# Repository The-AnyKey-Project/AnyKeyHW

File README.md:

# AnyKeyHW
Hardware for configurable macro keyboard with displays

## Inspired by
https://github.com/CoretechR/Keybon

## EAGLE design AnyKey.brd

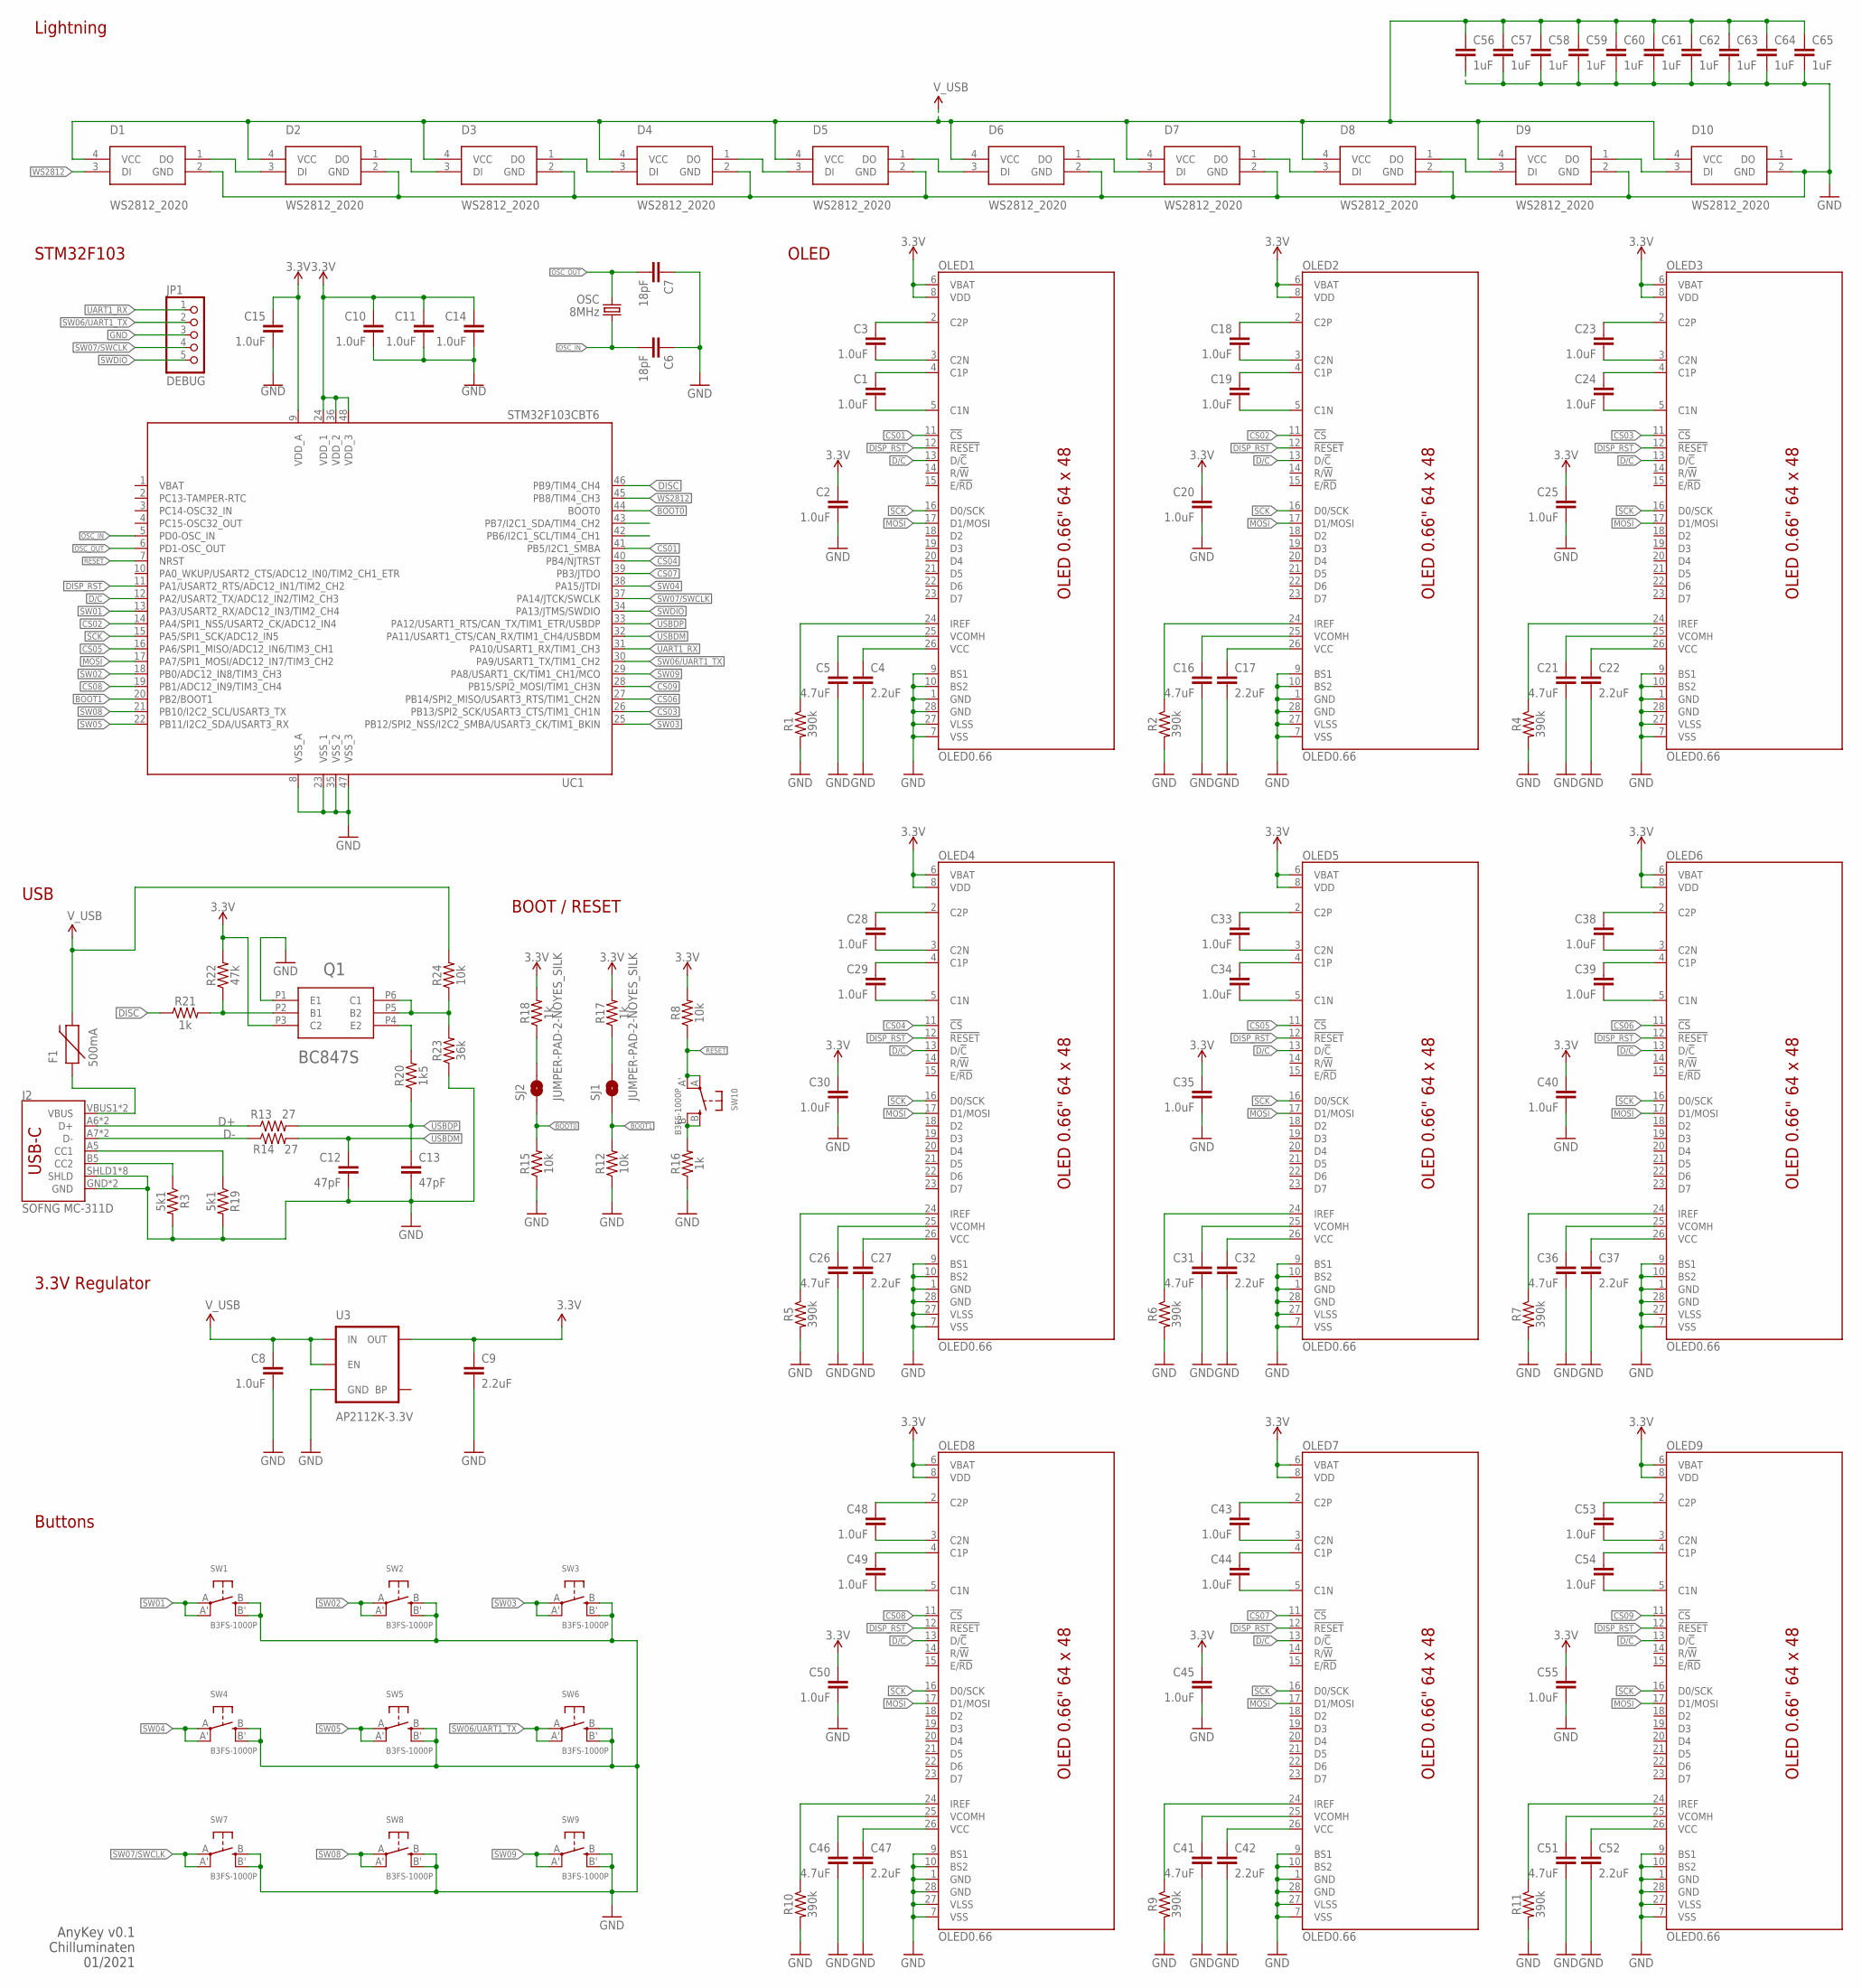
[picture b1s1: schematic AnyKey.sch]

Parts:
C1, C2, C3, C8, C10, C11, C14, C15, C18, C19, C20, C23, C24, C25, C28, C29, C30, C33, C34, C35, C38, C39, C40, C43, C44, C45, C48, C49, C50, C53, C54, C55: 1.0uF; 0603
C4, C9, C17, C22, C27, C32, C37, C42, C47, C52: 2.2uF; 0603
C5, C16, C21, C26, C31, C36, C41, C46, C51: 4.7uF; 0603
C6, C7: 18pF; 0603
C12, C13: 47pF; 0603
C56, C57, C58, C59, C60, C61, C62, C63, C64, C65: 1uF; 0603
D1, D2, D3, D4, D5, D6, D7, D8, D9, D10: WS2812_2020
F1: 500mA; PTC-1206
J2: SOFNG MC-311D; USB-C-16P
JP1: DEBUG; 1X05/90
OLED1, OLED2, OLED3, OLED4, OLED5, OLED6, OLED7, OLED8, OLED9: OLED0.66; OLED-0.66-64X48
OSC: 8MHz; CRYSTAL-SMD-5X3
Q1: BC847S; SOT-363
R1, R2, R4, R5, R6, R7, R9, R10, R11: 390k; 0603
R3, R19: 5k1; 0603
R8, R12, R15, R24: 10k; 0603
R13, R14: 27; 0603
R16, R17, R18, R21: 1k; 0603
R20: 1k5; 0603
R22: 47k; 0603
R23: 36k; 0603
SJ1, SJ2: JUMPER-PAD-2-NOYES_SILK; PAD-JUMPER-2-NO_YES_SILK
SW1, SW2, SW3, SW4, SW5, SW6, SW7, SW8, SW9, SW10: B3FS-1000P; EVQ-Q2_SMALLER
U3: AP2112K-3.3V; SOT23-5
UC1: STM32F103CBT6; LQFP48

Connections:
3.3V: C2.1, C9.1, C10.1, C11.1, C14.1, C15.1, C20.1, C25.1, C30.1, C35.1, C40.1, C45.1, C50.1, C55.1, OLED1.6 (VBAT), OLED1.8 (VDD), OLED2.6 (VBAT), OLED2.8 (VDD), OLED3.6 (VBAT), OLED3.8 (VDD), OLED4.6 (VBAT), OLED4.8 (VDD), OLED5.6 (VBAT), OLED5.8 (VDD), OLED6.6 (VBAT), OLED6.8 (VDD), OLED7.6 (VBAT), OLED7.8 (VDD), OLED8.6 (VBAT), OLED8.8 (VDD), OLED9.6 (VBAT), OLED9.8 (VDD), Q1.P3 (C2), R8.2, R17.2, R18.2, R22.2, U3.5 (OUT), UC1.9 (VDD_A), UC1.24 (VDD_1), UC1.36 (VDD_2), UC1.48 (VDD_3)
BOOT0: R15.2, SJ2.1, UC1.44 (BOOT0)
BOOT1: R12.2, SJ1.1, UC1.20 (PB2/BOOT1)
C1N: C1.2, OLED1.5 (C1N)
C1N1: C19.2, OLED2.5 (C1N)
C1N2: C24.2, OLED3.5 (C1N)
C1N3: C29.2, OLED4.5 (C1N)
C1N4: C34.2, OLED5.5 (C1N)
C1N5: C39.2, OLED6.5 (C1N)
C1N6: C44.2, OLED7.5 (C1N)
C1N7: C49.2, OLED8.5 (C1N)
C1N8: C54.2, OLED9.5 (C1N)
C1P: C1.1, OLED1.4 (C1P)
C1P1: C19.1, OLED2.4 (C1P)
C1P2: C24.1, OLED3.4 (C1P)
C1P3: C29.1, OLED4.4 (C1P)
C1P4: C34.1, OLED5.4 (C1P)
C1P5: C39.1, OLED6.4 (C1P)
C1P6: C44.1, OLED7.4 (C1P)
C1P7: C49.1, OLED8.4 (C1P)
C1P8: C54.1, OLED9.4 (C1P)
C2N: C3.2, OLED1.3 (C2N)
C2N1: C18.2, OLED2.3 (C2N)
C2N2: C23.2, OLED3.3 (C2N)
C2N3: C28.2, OLED4.3 (C2N)
C2N4: C33.2, OLED5.3 (C2N)
C2N5: C38.2, OLED6.3 (C2N)
C2N6: C43.2, OLED7.3 (C2N)
C2N7: C48.2, OLED8.3 (C2N)
C2N8: C53.2, OLED9.3 (C2N)
C2P: C3.1, OLED1.2 (C2P)
C2P1: C18.1, OLED2.2 (C2P)
C2P2: C23.1, OLED3.2 (C2P)
C2P3: C28.1, OLED4.2 (C2P)
C2P4: C33.1, OLED5.2 (C2P)
C2P5: C38.1, OLED6.2 (C2P)
C2P6: C43.1, OLED7.2 (C2P)
C2P7: C48.1, OLED8.2 (C2P)
C2P8: C53.1, OLED9.2 (C2P)
CS01: OLED1.11 (!CS!), UC1.41 (PB5/I2C1_SMBA)
CS02: OLED2.11 (!CS!), UC1.14 (PA4/SPI1_NSS/USART2_CK/ADC12_IN4)
CS03: OLED3.11 (!CS!), UC1.26 (PB13/SPI2_SCK/USART3_CTS/TIM1_CH1N)
CS04: OLED4.11 (!CS!), UC1.40 (PB4/NJTRST)
CS05: OLED5.11 (!CS!), UC1.16 (PA6/SPI1_MISO/ADC12_IN6/TIM3_CH1)
CS06: OLED6.11 (!CS!), UC1.27 (PB14/SPI2_MISO/USART3_RTS/TIM1_CH2N)
CS07: OLED7.11 (!CS!), UC1.39 (PB3/JTDO)
CS08: OLED8.11 (!CS!), UC1.19 (PB1/ADC12_IN9/TIM3_CH4)
CS09: OLED9.11 (!CS!), UC1.28 (PB15/SPI2_MOSI/TIM1_CH3N)
D+: J2.A6 (D+), J2.B6 (D+), R13.1
D-: J2.A7 (D-), J2.B7 (D-), R14.1
D/C: OLED1.13 (D/!C!), OLED2.13 (D/!C!), OLED3.13 (D/!C!), OLED4.13 (D/!C!), OLED5.13 (D/!C!), OLED6.13 (D/!C!), OLED7.13 (D/!C!), OLED8.13 (D/!C!), OLED9.13 (D/!C!), UC1.12 (PA2/USART2_TX/ADC12_IN2/TIM2_CH3)
DISC: R21.1, UC1.46 (PB9/TIM4_CH4)
DISP_RST: OLED1.12 (!RESET!), OLED2.12 (!RESET!), OLED3.12 (!RESET!), OLED4.12 (!RESET!), OLED5.12 (!RESET!), OLED6.12 (!RESET!), OLED7.12 (!RESET!), OLED8.12 (!RESET!), OLED9.12 (!RESET!), UC1.11 (PA1/USART2_RTS/ADC12_IN1/TIM2_CH2)
GND: C2.2, C4.2, C5.2, C6.1, C7.1, C8.2, C9.2, C10.2, C11.2, C12.2, C13.2, C14.2, C15.2, C16.2, C17.2, C20.2, C21.2, C22.2, C25.2, C26.2, C27.2, C30.2, C31.2, C32.2, C35.2, C36.2, C37.2, C40.2, C41.2, C42.2, C45.2, C46.2, C47.2, C50.2, C51.2, C52.2, C55.2, C56.2, C57.2, C58.2, C59.2, C60.2, C61.2, C62.2, C63.2, C64.2, C65.2, D1.2 (GND), D2.2 (GND), D3.2 (GND), D4.2 (GND), D5.2 (GND), D6.2 (GND), D7.2 (GND), D8.2 (GND), D9.2 (GND), D10.2 (GND), J2.GND, J2.GND2 (GND), J2.SHLD1 (SHLD), J2.SHLD2 (SHLD), J2.SHLD3 (SHLD), J2.SHLD4 (SHLD), J2.SHLD5 (SHLD), J2.SHLD6 (SHLD), J2.SHLD7 (SHLD), J2.SHLD8 (SHLD), JP1.3, OLED1.1 (GND), OLED1.7 (VSS), OLED1.9 (BS1), OLED1.10 (BS2), OLED1.27 (VLSS), OLED1.28 (GND), OLED2.1 (GND), OLED2.7 (VSS), OLED2.9 (BS1), OLED2.10 (BS2), OLED2.27 (VLSS), OLED2.28 (GND), OLED3.1 (GND), OLED3.7 (VSS), OLED3.9 (BS1), OLED3.10 (BS2), OLED3.27 (VLSS), OLED3.28 (GND), OLED4.1 (GND), OLED4.7 (VSS), OLED4.9 (BS1), OLED4.10 (BS2), OLED4.27 (VLSS), OLED4.28 (GND), OLED5.1 (GND), OLED5.7 (VSS), OLED5.9 (BS1), OLED5.10 (BS2), OLED5.27 (VLSS), OLED5.28 (GND), OLED6.1 (GND), OLED6.7 (VSS), OLED6.9 (BS1), OLED6.10 (BS2), OLED6.27 (VLSS), OLED6.28 (GND), OLED7.1 (GND), OLED7.7 (VSS), OLED7.9 (BS1), OLED7.10 (BS2), OLED7.27 (VLSS), OLED7.28 (GND), OLED8.1 (GND), OLED8.7 (VSS), OLED8.9 (BS1), OLED8.10 (BS2), OLED8.27 (VLSS), OLED8.28 (GND), OLED9.1 (GND), OLED9.7 (VSS), OLED9.9 (BS1), OLED9.10 (BS2), OLED9.27 (VLSS), OLED9.28 (GND), Q1.P1 (E1), R1.2, R2.2, R3.2, R4.2, R5.2, R6.2, R7.2, R9.2, R10.2, R11.2, R12.1, R15.1, R16.1, R19.2, R23.1, SW1.B (S), SW1.B' (S1), SW2.B (S), SW2.B' (S1), SW3.B (S), SW3.B' (S1), SW4.B (S), SW4.B' (S1), SW5.B (S), SW5.B' (S1), SW6.B (S), SW6.B' (S1), SW7.B (S), SW7.B' (S1), SW8.B (S), SW8.B' (S1), SW9.B (S), SW9.B' (S1), U3.2 (GND), UC1.8 (VSS_A), UC1.23 (VSS_1), UC1.35 (VSS_2), UC1.47 (VSS_3)
IREF: OLED1.24 (IREF), R1.1
IREF1: OLED2.24 (IREF), R2.1
IREF2: OLED3.24 (IREF), R4.1
IREF3: OLED4.24 (IREF), R5.1
IREF4: OLED5.24 (IREF), R6.1
IREF5: OLED6.24 (IREF), R7.1
IREF6: OLED7.24 (IREF), R9.1
IREF7: OLED8.24 (IREF), R10.1
IREF8: OLED9.24 (IREF), R11.1
MOSI: OLED1.17 (D1/MOSI), OLED2.17 (D1/MOSI), OLED3.17 (D1/MOSI), OLED4.17 (D1/MOSI), OLED5.17 (D1/MOSI), OLED6.17 (D1/MOSI), OLED7.17 (D1/MOSI), OLED8.17 (D1/MOSI), OLED9.17 (D1/MOSI), UC1.17 (PA7/SPI1_MOSI/ADC12_IN7/TIM3_CH2)
unnamed: R16.2, SW10.B (S), SW10.B' (S1)
unnamed: R18.1, SJ2.2
unnamed: R17.1, SJ1.2
unnamed: C4.1, OLED1.26 (VCC)
unnamed: C17.1, OLED2.26 (VCC)
unnamed: C22.1, OLED3.26 (VCC)
unnamed: C37.1, OLED6.26 (VCC)
unnamed: C32.1, OLED5.26 (VCC)
unnamed: J2.A5 (CC1), R19.1
unnamed: C27.1, OLED4.26 (VCC)
unnamed: J2.B5 (CC2), R3.1
unnamed: C47.1, OLED8.26 (VCC)
unnamed: C42.1, OLED7.26 (VCC)
unnamed: C52.1, OLED9.26 (VCC)
unnamed: Q1.P4 (E2), R20.2
unnamed: Q1.P5 (B2), Q1.P6 (C1), R23.2, R24.1
unnamed: Q1.P2 (B1), R21.2, R22.1
unnamed: D1.1 (DO), D2.3 (DI)
unnamed: D2.1 (DO), D3.3 (DI)
unnamed: D3.1 (DO), D4.3 (DI)
unnamed: D4.1 (DO), D5.3 (DI)
unnamed: D5.1 (DO), D6.3 (DI)
unnamed: D6.1 (DO), D7.3 (DI)
unnamed: D7.1 (DO), D8.3 (DI)
unnamed: D8.1 (DO), D9.3 (DI)
unnamed: D9.1 (DO), D10.3 (DI)
OSC_IN: C6.2, OSC.1, UC1.5 (PD0-OSC_IN)
OSC_OUT: C7.2, OSC.3 (2), UC1.6 (PD1-OSC_OUT)
RESET: R8.1, SW10.A, SW10.A' (P1), UC1.7 (NRST)
SCK: OLED1.16 (D0/SCK), OLED2.16 (D0/SCK), OLED3.16 (D0/SCK), OLED4.16 (D0/SCK), OLED5.16 (D0/SCK), OLED6.16 (D0/SCK), OLED7.16 (D0/SCK), OLED8.16 (D0/SCK), OLED9.16 (D0/SCK), UC1.15 (PA5/SPI1_SCK/ADC12_IN5)
SW01: SW1.A, SW1.A' (P1), UC1.13 (PA3/USART2_RX/ADC12_IN3/TIM2_CH4)
SW02: SW2.A, SW2.A' (P1), UC1.18 (PB0/ADC12_IN8/TIM3_CH3)
SW03: SW3.A, SW3.A' (P1), UC1.25 (PB12/SPI2_NSS/I2C2_SMBA/USART3_CK/TIM1_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)
SW04: SW4.A, SW4.A' (P1), UC1.38 (PA15/JTDI)
SW05: SW5.A, SW5.A' (P1), UC1.22 (PB11/I2C2_SDA/USART3_RX)
SW06/UART1_TX: JP1.2, SW6.A, SW6.A' (P1), UC1.30 (PA9/USART1_TX/TIM1_CH2)
SW07/SWCLK: JP1.4, SW7.A, SW7.A' (P1), UC1.37 (PA14/JTCK/SWCLK)
SW08: SW8.A, SW8.A' (P1), UC1.21 (PB10/I2C2_SCL/USART3_TX)
SW09: SW9.A, SW9.A' (P1), UC1.29 (PA8/USART1_CK/TIM1_CH1/MCO)
SWDIO: JP1.5, UC1.34 (PA13/JTMS/SWDIO)
UART1_RX: JP1.1, UC1.31 (PA10/USART1_RX/TIM1_CH3)
USBDM: C12.1, R14.2, UC1.32 (PA11/USART1_CTS/CAN_RX/TIM1_CH4/USBDM)
USBDP: C13.1, R13.2, R20.1, UC1.33 (PA12/USART1_RTS/CAN_TX/TIM1_ETR/USBDP)
VBAT: UC1.1 (VBAT)
VCOMH: C5.1, OLED1.25 (VCOMH)
VCOMH1: C16.1, OLED2.25 (VCOMH)
VCOMH2: C21.1, OLED3.25 (VCOMH)
VCOMH3: C26.1, OLED4.25 (VCOMH)
VCOMH4: C31.1, OLED5.25 (VCOMH)
VCOMH5: C36.1, OLED6.25 (VCOMH)
VCOMH6: C41.1, OLED7.25 (VCOMH)
VCOMH7: C46.1, OLED8.25 (VCOMH)
VCOMH8: C51.1, OLED9.25 (VCOMH)
VUSB-RAW: F1.1, J2.VBUS1 (VBUS), J2.VBUS2 (VBUS)
V_USB: C8.1, C56.1, C57.1, C58.1, C59.1, C60.1, C61.1, C62.1, C63.1, C64.1, C65.1, D1.4 (VCC), D2.4 (VCC), D3.4 (VCC), D4.4 (VCC), D5.4 (VCC), D6.4 (VCC), D7.4 (VCC), D8.4 (VCC), D9.4 (VCC), D10.4 (VCC), F1.2, R24.2, U3.1 (IN), U3.3 (EN)
WS2812: D1.3 (DI), UC1.45 (PB8/TIM4_CH3)

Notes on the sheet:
Buttons
OLED
STM32F103
USB
BOOT / RESET
3.3V Regulator
AnyKey v0.1 Chilluminaten 01/2021
Lightning

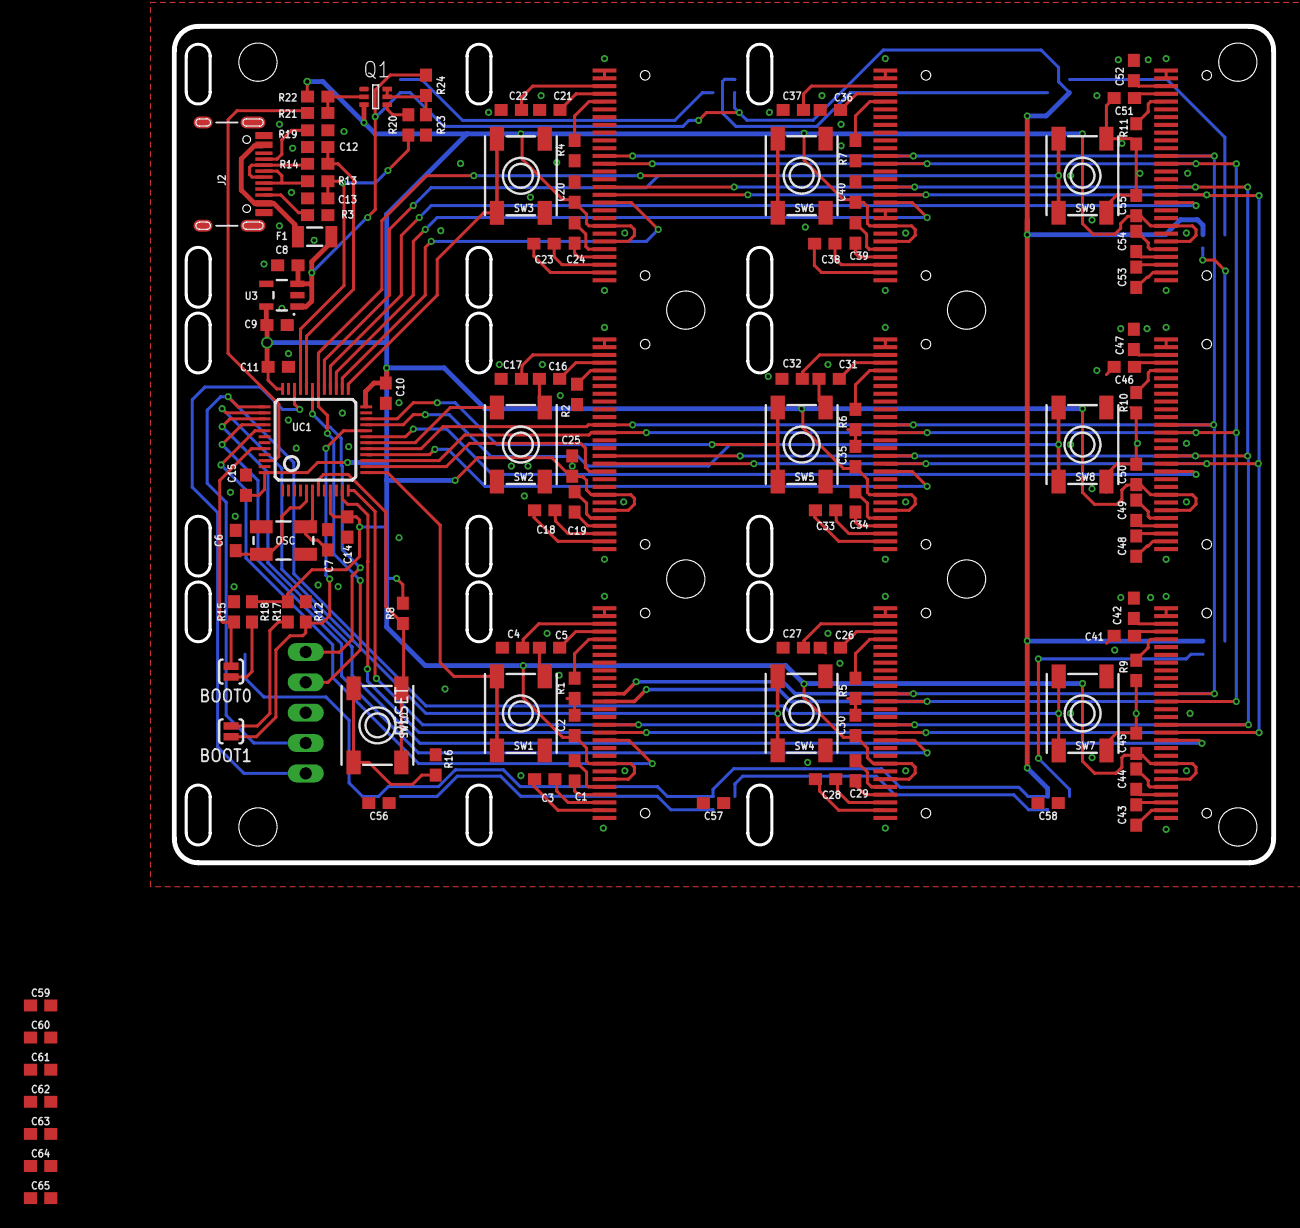
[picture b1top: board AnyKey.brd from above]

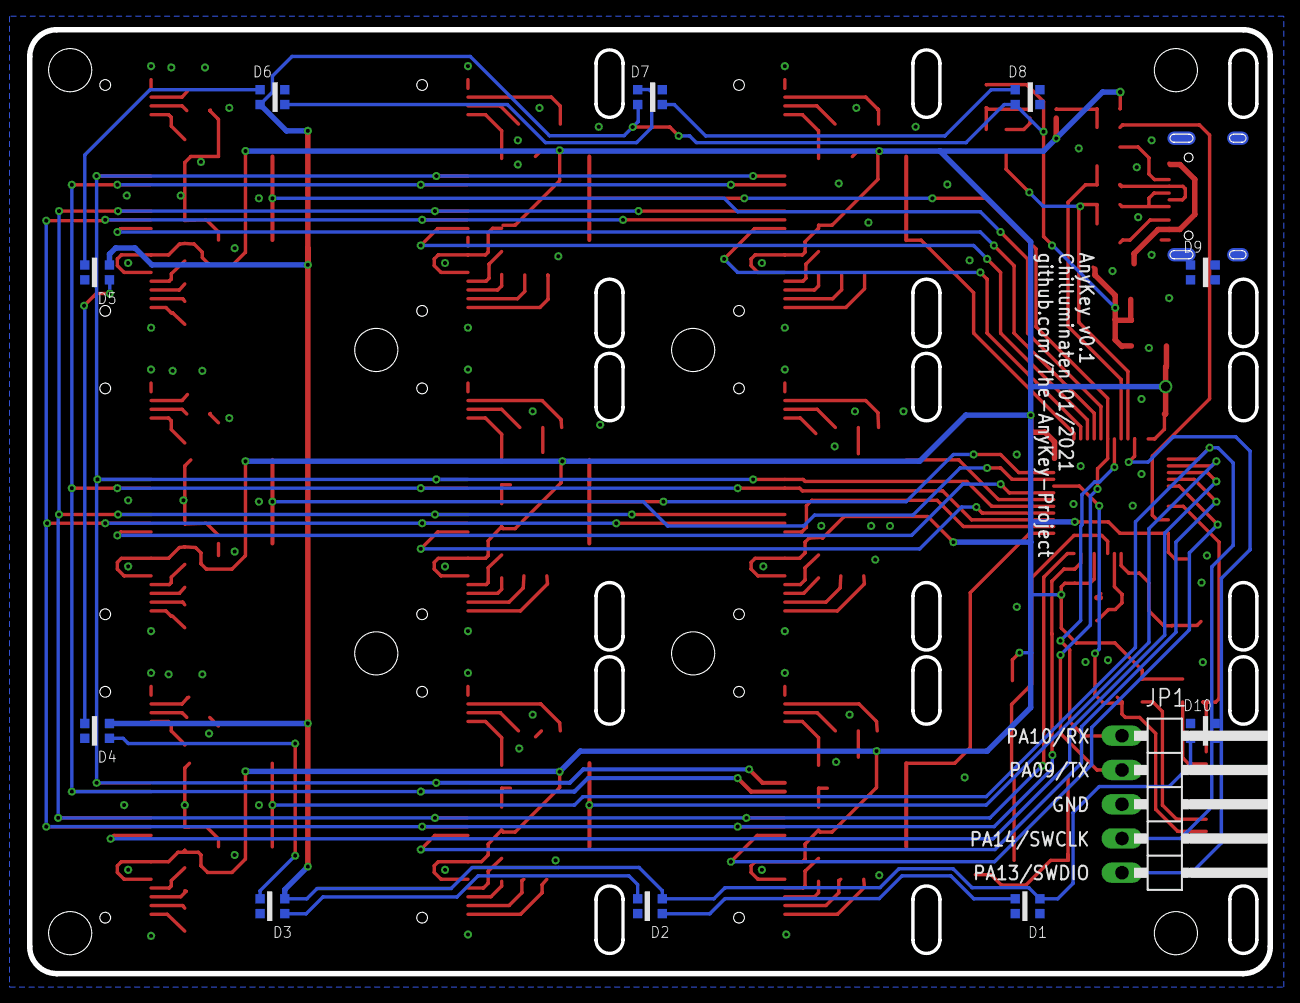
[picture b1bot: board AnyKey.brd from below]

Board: 2 copper layers, 92.0 x 70.0 mm, 127 parts (11 on the bottom side), 119 nets.

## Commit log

2021-01-22 El Barto was here
2021-01-23 Move all used parts to one lib
2021-01-23 Add gitignore
2021-01-23 Initial cleanup, correctted some misplaced names in top silkscreen
2021-01-23 Initial commit for CAD Files
2021-01-23 New Cover with smaller windows
2021-04-02 Implemented Auto-Reset, Added WS2812 (WORK IN PROGRESS)
